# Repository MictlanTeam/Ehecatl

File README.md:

# EHECATL - Line Follower Racing Robot

**EHECATL** (pronunciado "Ehécatl") es un robot seguidor de línea diseñado para competencias de racing. Su nombre proviene del dios azteca del viento, representando su característica principal: un sistema de succión mediante turbina para generar efecto ground y aumentar la tracción en curvas a alta velocidad.

## 🏆 Características Principales

### Hardware
- **Microcontrolador**: ESP32-S3-Zero
- **Sensores**: Array de 16 sensores IR con multiplexadores duales
- **Motores**: 2 motores DC con drivers RZ7886
- **Turbina**: Sistema de succión con ESC brushless (efecto ground)
- **Control**: Botón físico, señal externa de start, y comandos serial

### Software
- **Control PID**: Controlador proporcional-derivativo ajustable
- **Pre-inicio Inteligente**: Estabilización y activación de turbina antes del arranque
- **Aceleración Adaptativa**: Velocidad mínima de 20% para arranques rápidos
- **Protocolo ESC**: Control de turbina a 50Hz (protocolo servo estándar)
- **Lectura Simétrica**: Sensores leídos desde el centro hacia extremos
- **Calibración Automática**: Auto-calibración con umbral adaptativo

## 🛠️ Especificaciones Técnicas

### Mapa de Pines

| Componente | Pin | Tipo | Descripción |
|------------|-----|------|-------------|
| **Motores** |
| Motor Izq A | 1 | PWM | Control motor izquierdo |
| Motor Izq B | 4 | PWM | Control motor izquierdo |
| Motor Der A | 9 | PWM | Control motor derecho |
| Motor Der B | 2 | PWM | Control motor derecho |
| **Sensores** |
| MUX_A | 3 | Digital Out | Control multiplexador (LSB) |
| MUX_B | 11 | Digital Out | Control multiplexador |
| MUX_C | 10 | Digital Out | Control multiplexador (MSB) |
| Sensores 1-8 | 8 | Analog In | Lectura multiplexador 1 |
| Sensores 9-16 | 7 | Analog In | Lectura multiplexador 2 |
| **Utilidades** |
| LED | 5 | Digital Out | LED de estado |
| Botón | 13 | Digital In | Botón con pull-up |
| Start Signal | 6 | Digital In | Señal de inicio externa |
| Turbina | 12 | PWM (ESC) | Control turbina/succión |

### Configuraciones PWM

#### Motores
- **Frecuencia**: 5 kHz
- **Resolución**: 10 bits (0-1023)
- **Canales**: 0-3

#### Turbina (ESC)
- **Frecuencia**: 50 Hz (protocolo servo)
- **Resolución**: 11 bits
- **Rango**: 102-204 (1000μs-2000μs)
- **Canal**: 4

### Parámetros PID

```cpp
KP = 0.2    // Ganancia proporcional
KD = 0.80   // Ganancia derivativa
```

### Tiempos de Control

- **Loop de control**: 1000 μs (1 kHz)
- **Timeout pérdida de línea**: 250 ms
- **Calibración sensores**: 3000 ms
- **Tiempo máximo de prueba**: 30000 ms

## ⚙️ Configuración

### Configuración de Flash (platformio.ini)

```ini
[env:esp32-s3-zero]
platform = espressif32
board = esp32-s3-devkitc-1
framework = arduino
board_build.mcu = esp32s3
board_build.f_cpu = 240000000L
board_build.flash_mode = qio
board_upload.flash_size = 4MB
board_build.arduino.memory_type = qio_opi
board_build.psram_type = opi
board_build.partitions = default.csv
monitor_speed = 115200
upload_speed = 921600
```

### Ajuste de Parámetros

Los parámetros principales se pueden ajustar en:

- **`control.h`**: Constantes PID, tiempos de control
- **`motors.h`**: Configuración PWM de motores y turbina
- **`sensors.h`**: Configuración de sensores

## 📱 Uso Básico

### Inicio del Robot

1. **Encendido**: Conectar alimentación
2. **Inicialización**: Esperar 2 segundos (ESC de turbina)
3. **Calibración**: Presionar botón → Mover robot sobre línea 3 segundos
4. **Listo**: LED indica que está listo para iniciar

### Modos de Inicio

El robot puede iniciarse de 3 formas:

1. **Botón Largo (>1s)**:
   - Presionar y mantener botón
   - Cuenta regresiva de 3 segundos
   - Último segundo: pre-inicio con turbina al 85%
   - ¡GO!

2. **Señal Externa (Pin 6)**:
   - Compatible con sistemas de competencia
   - Inicio inmediato al detectar HIGH en pin 6

3. **Comando Serial (`s`)**:
   - Enviar comando `s` por monitor serial
   - Cuenta regresiva de 3 segundos
   - Inicio automático

### Comandos Serial

| Comando | Función | Ejemplo |
|---------|---------|---------|
| `s` | Iniciar carrera | - |
| `x` | Detener carrera | - |
| `r` | Mostrar sensores RAW | - |
| `c` | Mostrar sensores calibrados | - |
| `v[num]` | Cambiar velocidad base (0-100%) | `v40` |
| `a[num]` | Cambiar aceleración (0-100%) | `a70` |
| `f[num]` | Cambiar velocidad turbina (0-100%) | `f90` |
| `cal` | Re-calibrar sensores | - |

## 📊 Rendimiento

## 📝 Licencia

Este proyecto está bajo la Licencia MIT. Ver archivo `LICENSE` para más detalles.

## 🔗 Enlaces Útiles

- [Documentación ESP32-S3](https://docs.espressif.com/projects/esp-idf/en/latest/esp32s3/)
- [PlatformIO Docs](https://docs.platformio.org/)
- [ESP32-S3-Zero](https://www.waveshare.com/wiki/ESP32-S3-Zero)

---

**EHECATL** - El viento que domina la pista 💨🏎️

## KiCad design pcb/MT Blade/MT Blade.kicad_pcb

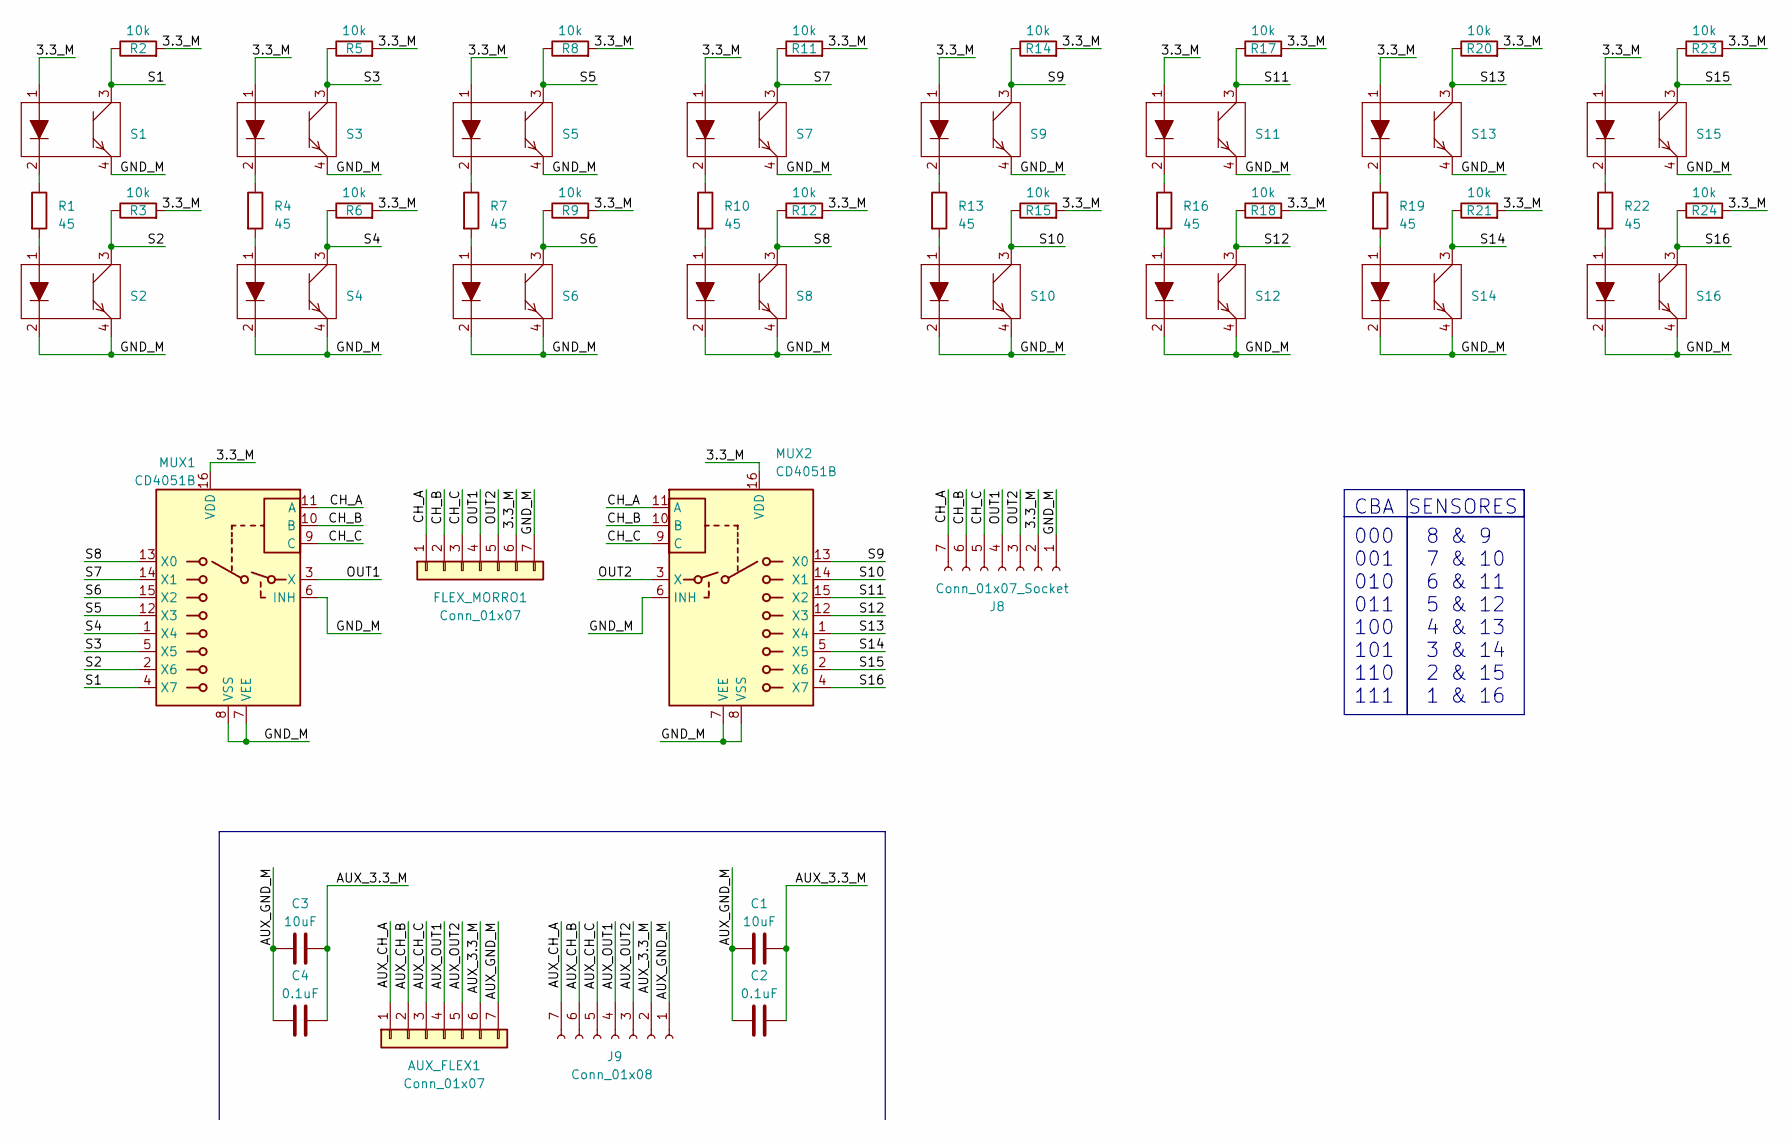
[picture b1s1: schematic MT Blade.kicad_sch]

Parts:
AUX_FLEX1: Conn_01x07; TE_0-1734839-7_1x07-1MP_P0.5mm_Horizontal; LCSC Part # C388693
C1, C3: 10uF; C_0805_2012Metric_Pad1.18x1.45mm_HandSolder; LCSC Part # C380331
C2, C4: 0.1uF; C_0805_2012Metric_Pad1.18x1.45mm_HandSolder; LCSC Part # C2847428
FLEX_MORRO1: Conn_01x07; TE_0-1734839-7_1x07-1MP_P0.5mm_Horizontal; LCSC Part # C388693
J8: Conn_01x07_Socket; PinHeader_1x07_P2.54mm_Vertical
J9: Conn_01x08; PinHeader_1x07_P2.54mm_Vertical
MUX1, MUX2: CD4051B; MUX_CD4051B; LCSC Part # C3007951
R1, R4, R7, R10, R13, R16, R19, R22: 45; R_0805_2012Metric_Pad1.20x1.40mm_HandSolder; LCSC Part # C3017827
R2, R3, R5, R6, R8, R9, R11, R12, R14, R15, R17, R18, R20, R21, R23, R24: 10k; R_0805_2012Metric_Pad1.20x1.40mm_HandSolder; LCSC Part # C17414
S1, S2, S3, S4, S5, S6, S7, S8, S9, S10, S11, S12, S13, S14, S15, S16: ITR8307_SMD; LCSC Part # C81632

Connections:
/3.3_M: FLEX_MORRO1.6, J8.2, MUX1.16 (VDD), MUX2.16 (VDD), R2.2, R3.2, R5.2, R6.2, R8.2, R9.2, R11.2, R12.2, R14.2, R15.2, R17.2, R18.2, R20.2, R21.2, R23.2, R24.2, S1.1, S3.1, S5.1, S7.1, S9.1, S11.1, S13.1, S15.1
/AUX_3.3_M: AUX_FLEX1.6, C1.1, C2.1, C3.1, C4.1, J9.2
/AUX_CH_A: AUX_FLEX1.1, J9.7
/AUX_CH_B: AUX_FLEX1.2, J9.6
/AUX_CH_C: AUX_FLEX1.3, J9.5
/AUX_GND_M: AUX_FLEX1.7, C1.2, C2.2, C3.2, C4.2, J9.1
/AUX_OUT1: AUX_FLEX1.4, J9.4
/AUX_OUT2: AUX_FLEX1.5, J9.3
/CH_A: FLEX_MORRO1.1, J8.7, MUX1.11 (A), MUX2.11 (A)
/CH_B: FLEX_MORRO1.2, J8.6, MUX1.10 (B), MUX2.10 (B)
/CH_C: FLEX_MORRO1.3, J8.5, MUX1.9 (C), MUX2.9 (C)
/GND_M: FLEX_MORRO1.7, J8.1, MUX1.6 (INH), MUX1.7 (VEE), MUX1.8 (VSS), MUX2.6 (INH), MUX2.7 (VEE), MUX2.8 (VSS), S1.4, S2.2, S2.4, S3.4, S4.2, S4.4, S5.4, S6.2, S6.4, S7.4, S8.2, S8.4, S9.4, S10.2, S10.4, S11.4, S12.2, S12.4, S13.4, S14.2, S14.4, S15.4, S16.2, S16.4
/OUT1: FLEX_MORRO1.4, J8.4, MUX1.3 (X)
/OUT2: FLEX_MORRO1.5, J8.3, MUX2.3 (X)
/S1: MUX1.4 (X7), R2.1, S1.3
/S2: MUX1.2 (X6), R3.1, S2.3
/S3: MUX1.5 (X5), R5.1, S3.3
/S4: MUX1.1 (X4), R6.1, S4.3
/S5: MUX1.12 (X3), R8.1, S5.3
/S6: MUX1.15 (X2), R9.1, S6.3
/S7: MUX1.14 (X1), R11.1, S7.3
/S8: MUX1.13 (X0), R12.1, S8.3
/S9: MUX2.13 (X0), R14.1, S9.3
/S10: MUX2.14 (X1), R15.1, S10.3
/S11: MUX2.15 (X2), R17.1, S11.3
/S12: MUX2.12 (X3), R18.1, S12.3
/S13: MUX2.1 (X4), R20.1, S13.3
/S14: MUX2.5 (X5), R21.1, S14.3
/S15: MUX2.2 (X6), R23.1, S15.3
/S16: MUX2.4 (X7), R24.1, S16.3
unnamed: R1.1, S1.2
unnamed: R1.2, S2.1
unnamed: R4.1, S3.2
unnamed: R4.2, S4.1
unnamed: R7.1, S5.2
unnamed: R7.2, S6.1
unnamed: R10.1, S7.2
unnamed: R10.2, S8.1
unnamed: R13.1, S9.2
unnamed: R13.2, S10.1
unnamed: R16.1, S11.2
unnamed: R16.2, S12.1
unnamed: R19.1, S13.2
unnamed: R19.2, S14.1
unnamed: R22.1, S15.2
unnamed: R22.2, S16.1

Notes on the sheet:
CBA
SENSORES
8 & 9 7 & 10 6 & 11 5 & 12 4 & 13 3 & 14 2 & 15 1 & 16
000 001 010 011 100 101 110 111

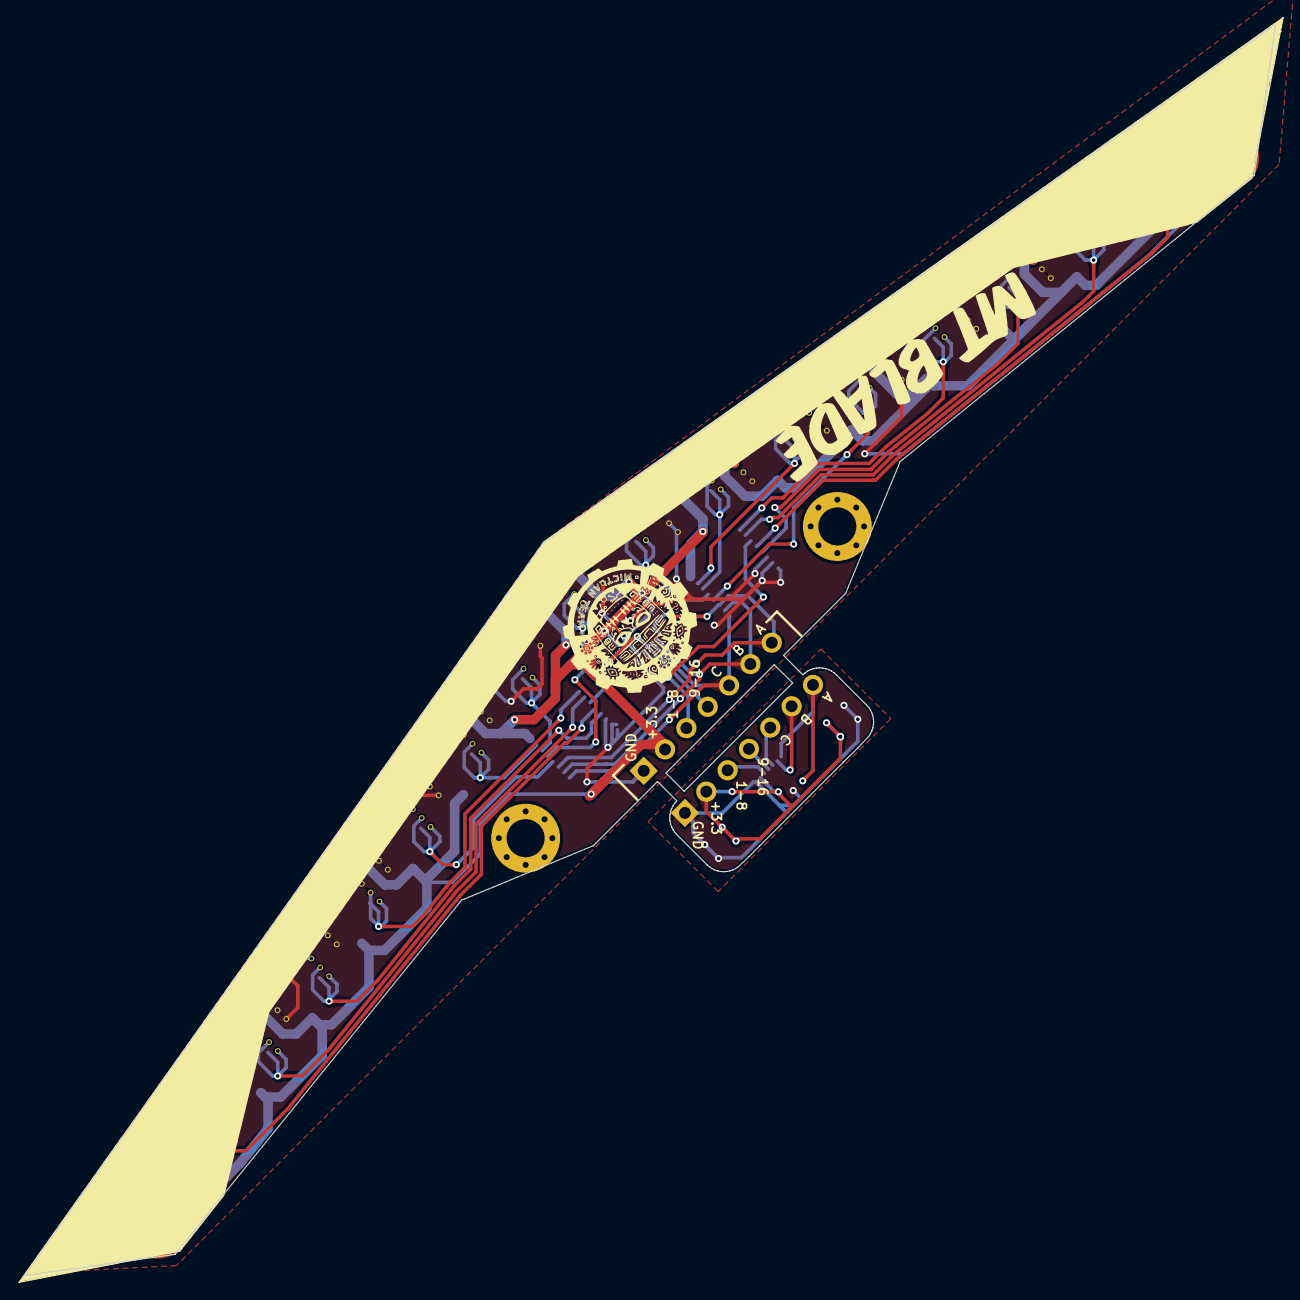
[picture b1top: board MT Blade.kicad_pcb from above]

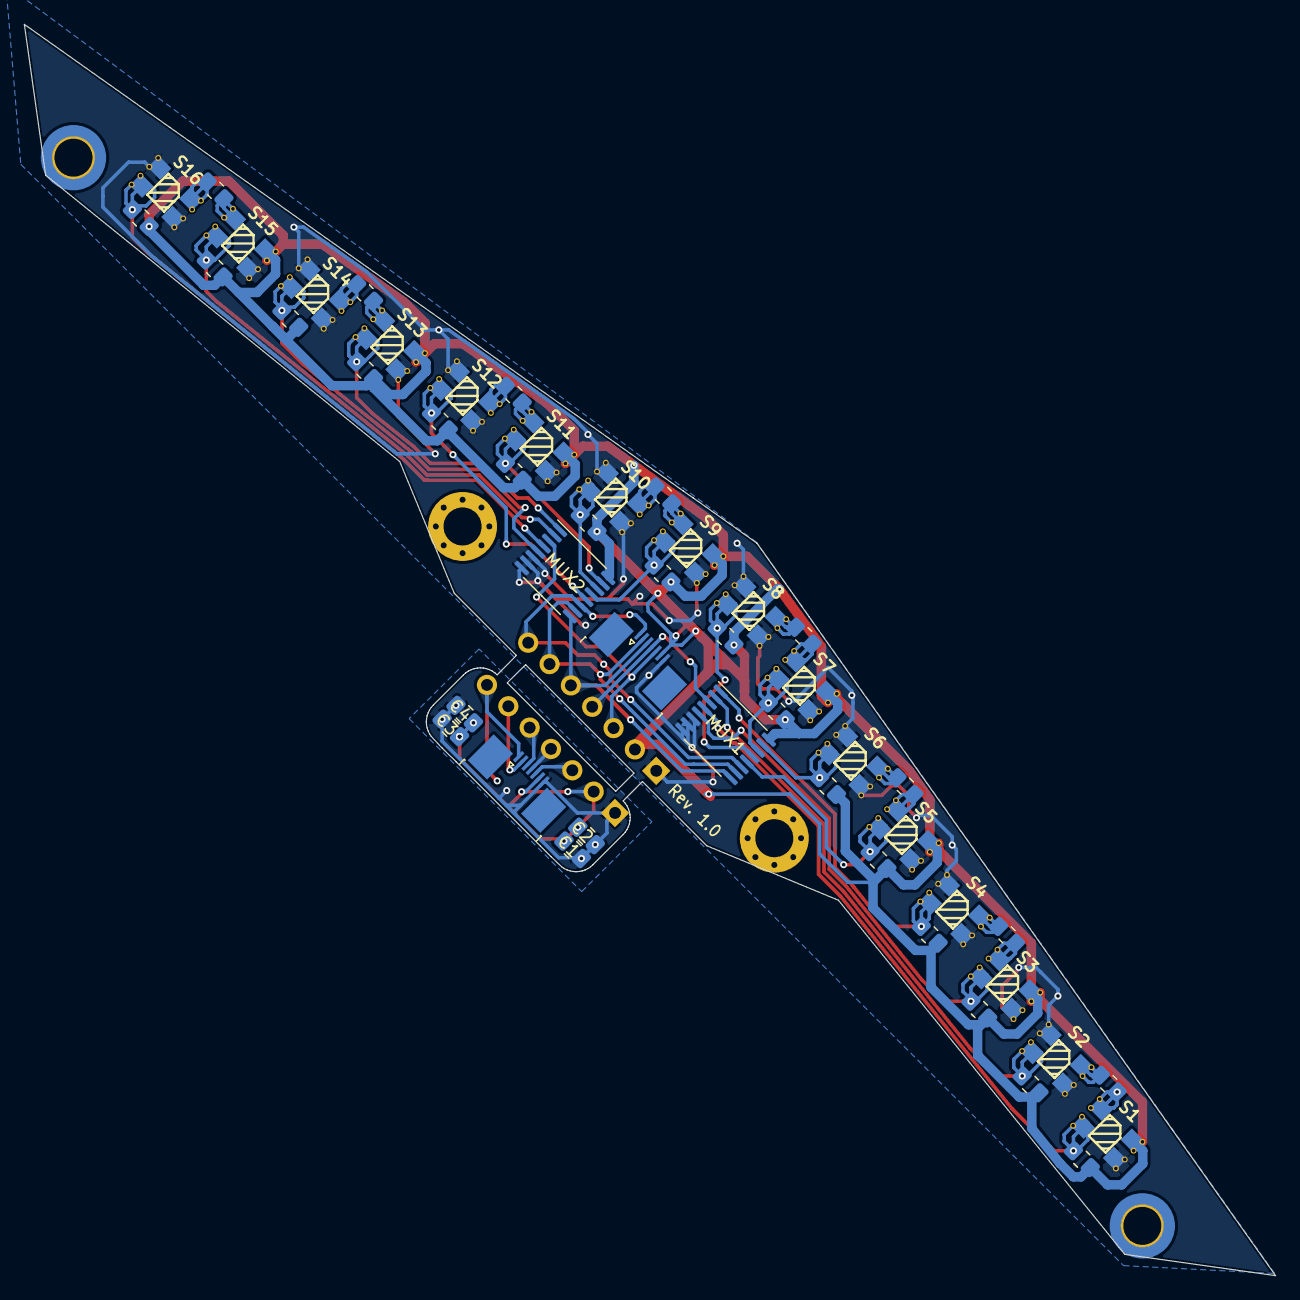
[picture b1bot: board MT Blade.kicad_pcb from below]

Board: 2 copper layers, 105.3 x 105.3 mm, 51 parts (49 on the bottom side), 46 nets.

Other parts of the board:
G: LOGO; MT_Silkscreen 10mm

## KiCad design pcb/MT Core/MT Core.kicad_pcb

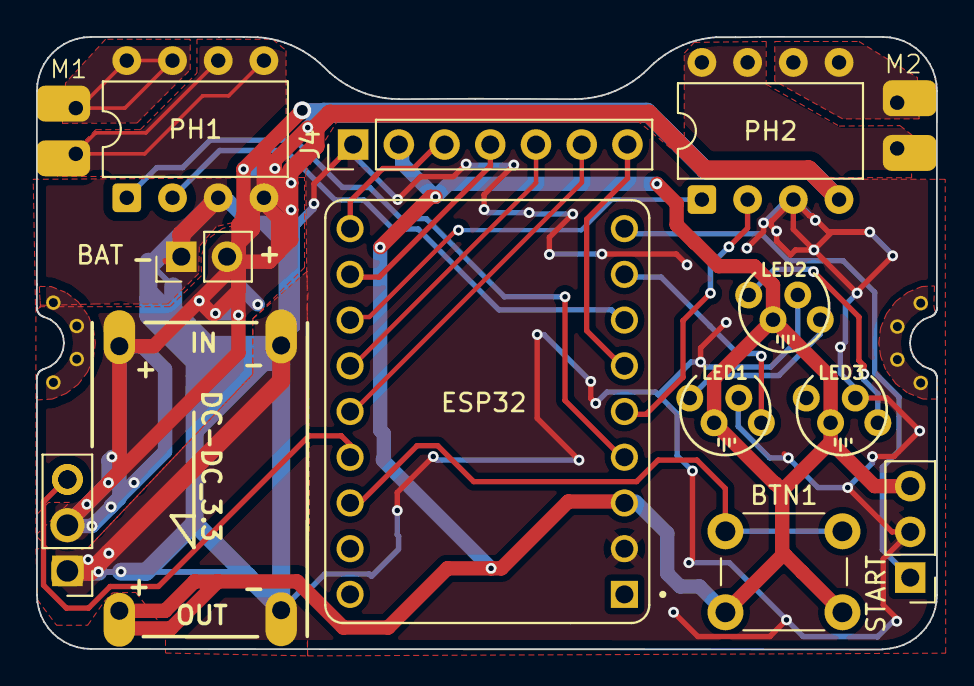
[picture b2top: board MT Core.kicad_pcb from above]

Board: 2 copper layers, 50.0 x 34.0 mm, 15 parts (0 on the bottom side), 22 nets.

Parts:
BAT: Conn_01x02_Socket; PinHeader_1x02_P2.54mm_Vertical
BTN1: SW_PUSH_6mm_H4.3mm
DC-DC_3.3: DC-DC_3.3 CN3903
ESP32: ESP32-S3-ZERO
J1: Conn_01x03_Socket; PinHeader_1x03_P2.54mm_Vertical
J4: Conn_01x07_Socket; PinHeader_1x07_P2.54mm_Vertical
LED1, LED2, LED3: LED_D5.0mm-4_RGB_Staggered_Pins
M1, M2: Conn_01x02_Socket; motor_pads
PH1, PH2: DIP-8_W7.62mm
START: Conn_01x03_Socket; PinHeader_1x03_P2.54mm_Vertical
SUCC: Conn_01x03_Socket; PinHeader_1x03_P2.54mm_Vertical

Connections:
+3.3V: BTN1.2, DC-DC_3.3.3 (OUT+), ESP32.3V3 (3V3(OUT)), J4.2, LED1.2 (VDD), LED2.2 (VDD), LED3.2 (VDD), START.3
/BATT: BAT.2, DC-DC_3.3.1 (IN+), J1.2, PH1.4 (VCC), PH2.4 (VCC), SUCC.2
/BTN: BTN1.1, ESP32.13 (GP13)
/LEDS: ESP32.5 (GP5), LED1.4 (DIN)
/PIN0: ESP32.7 (GP7), J4.3
/PIN1: ESP32.8 (GP8), J4.4
/PIN3: ESP32.10 (GP10), J4.5
/PIN4: ESP32.11 (GP11), J4.6
/PIN9: ESP32.3 (GP3), J4.7
/PWM_M1A: ESP32.1 (GP1), PH1.1 (S1)
/PWM_M1B: ESP32.4 (GP4), PH1.2 (S2)
/PWM_M2A: ESP32.9 (GP9), PH2.1 (S1)
/PWM_M2B: ESP32.2 (GP2), PH2.2 (S2)
/START: ESP32.6 (GP6), START.1
/SUCC: ESP32.12 (GP12), J1.3, SUCC.3
GND: BAT.1, DC-DC_3.3.2 (IN-), DC-DC_3.3.4 (OUT-), ESP32.GND, J1.1, J4.1, LED1.3 (GND), LED2.3 (GND), LED3.3 (GND), PH1.3 (GND), PH2.3 (GND), START.2, SUCC.1
unnamed: LED1.1 (DOUT), LED2.4 (DIN)
unnamed: LED2.1 (DOUT), LED3.4 (DIN)
unnamed: M1.1, PH1.5 (M+), PH1.6 (M+)
unnamed: M1.2, PH1.7 (M-), PH1.8 (M-)
unnamed: M2.1, PH2.5 (M+), PH2.6 (M+)
unnamed: M2.2, PH2.7 (M-), PH2.8 (M-)

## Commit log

2025-10-27 Add lock file for MT Blade PCB design to prevent concurrent edits
2025-10-27 Add lock file for MT Blade schematic with hostname and username
2025-10-28 code
2025-10-28 Remove advanced features and contribution guidelines
    Removed advanced functionalities, development guidelines, troubleshooting, contributions, credits, and contact information sections from README.
2025-10-28 Remove project structure details from README
    Removed project structure section from README.
2025-10-28 Remove support and troubleshooting section
    Removed support section and troubleshooting tips from the user manual.
2025-10-28 Remove 'alta velocidad' from project description
2025-10-28 Remove installation section from README.md
    Removed installation instructions and requirements from README.

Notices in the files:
README.md:
License: MIT
